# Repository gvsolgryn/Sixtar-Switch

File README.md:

# Sixtar-Switch
식스타 게이트 닌텐도 스위치 버전용 컨트롤러
# 지원기기
Nintendo Switch 및 Steam 을 지원하는 OS (Windows 10 및 11 에서 rp2040 펌웨어 테스트 완료)
# 디자인
키보드 형식을 기반으로 제작하였습니다 GAMO2 K28 을 보고 감명받아 제작을 시작하였습니다.
프로토타입으로만 제작해서 테스트 할 예정입니다.
(PCB는 만들 줄 알지만, 외관 및 기구 디자인은 잘 못하기도 하고, 아크릴 제작 단가가 높아서...)

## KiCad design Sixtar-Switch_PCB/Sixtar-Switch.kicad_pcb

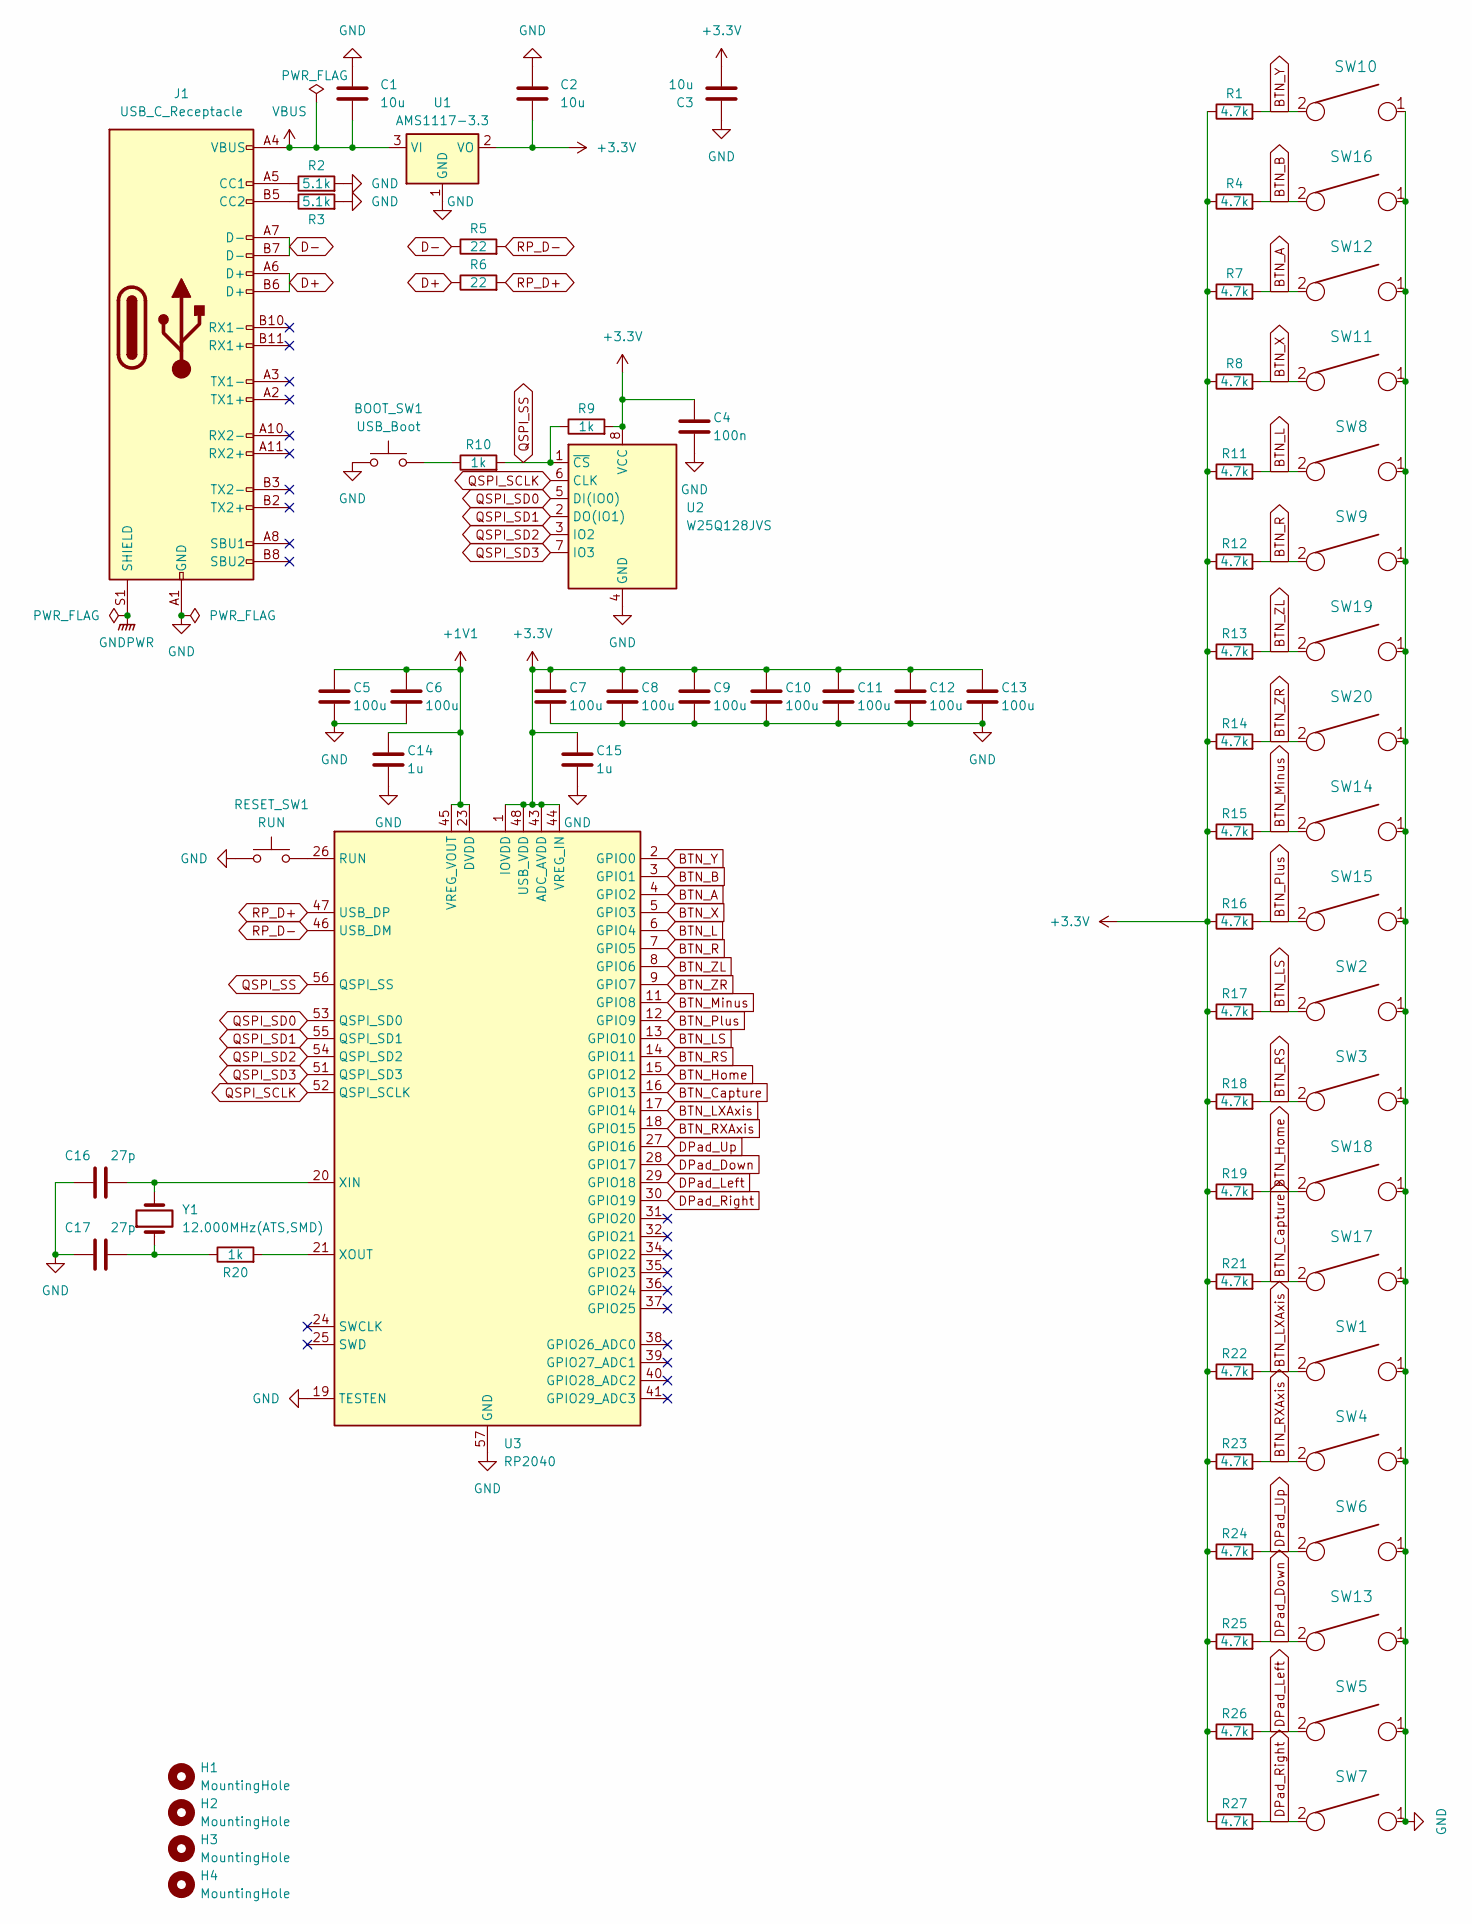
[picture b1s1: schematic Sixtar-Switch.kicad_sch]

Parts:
BOOT_SW1: USB_Boot; PinSocket_1x02_P2.54mm_Vertical
C1, C2, C3: 10u; C_0805_2012Metric_Pad1.18x1.45mm_HandSolder
C4: 100n; C_0805_2012Metric_Pad1.18x1.45mm_HandSolder
C5, C6, C7, C8, C9, C10, C11, C12, C13: 100u; C_0805_2012Metric_Pad1.18x1.45mm_HandSolder
C14, C15: 1u; C_0805_2012Metric_Pad1.18x1.45mm_HandSolder
C16, C17: 27p; C_0805_2012Metric_Pad1.18x1.45mm_HandSolder
H1, H2, H3, H4: MountingHole; MountingHole_3.2mm_M3
J1: USB_C_Receptacle; USB_C_Receptacle_XKB_U262-16XN-4BVC11
R1, R4, R7, R8, R11, R12, R13, R14, R15, R16, R17, R18, R19, R21, R22, R23, R24, R25, R26, R27: 4.7k; R_0805_2012Metric_Pad1.20x1.40mm_HandSolder
R2, R3: 5.1k; R_0805_2012Metric_Pad1.20x1.40mm_HandSolder
R5, R6: 22; R_0805_2012Metric_Pad1.20x1.40mm_HandSolder
R9, R10, R20: 1k; R_0805_2012Metric_Pad1.20x1.40mm_HandSolder
RESET_SW1: RUN; PinSocket_1x02_P2.54mm_Vertical
SW1, SW4, SW19, SW20: KEYSW; SW_Cherry_MX_2.00u_PCB
SW2, SW3, SW5, SW6, SW7, SW8, SW9, SW10, SW11, SW12, SW13, SW14, SW15, SW16, SW17, SW18: KEYSW; SW_Cherry_MX_1.00u_PCB
U1: AMS1117-3.3; SOT-223-3_TabPin2
U2: W25Q128JVS; SOIC-8_5.23x5.23mm_P1.27mm
U3: RP2040; QFN-56-1EP_7x7mm_P0.4mm_EP3.2x3.2mm
Y1: 12.000MHz(ATS,SMD); Crystal_SMD_5032-2Pin_5.0x3.2mm

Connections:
+1V1: C5.1, C6.1, C14.1, U3.23 (DVDD), U3.45 (VREG_VOUT), U3.50 (DVDD)
+3.3V: C2.2, C3.2, C4.1, C7.1, C8.1, C9.1, C10.1, C11.1, C12.1, C13.1, C15.1, R1.1, R4.1, R7.1, R8.1, R9.2, R11.1, R12.1, R13.1, R14.1, R15.1, R16.1, R17.1, R18.1, R19.1, R21.1, R22.1, R23.1, R24.1, R25.1, R26.1, R27.1, U1.2 (VO), U2.8 (VCC), U3.1 (IOVDD), U3.10 (IOVDD), U3.22 (IOVDD), U3.33 (IOVDD), U3.42 (IOVDD), U3.43 (ADC_AVDD), U3.44 (VREG_IN), U3.48 (USB_VDD), U3.49 (IOVDD)
BTN_A: R7.2, SW12.2, U3.4 (GPIO2)
BTN_B: R4.2, SW16.2, U3.3 (GPIO1)
BTN_Capture: R21.2, SW17.2, U3.16 (GPIO13)
BTN_Home: R19.2, SW18.2, U3.15 (GPIO12)
BTN_L: R11.2, SW8.2, U3.6 (GPIO4)
BTN_LS: R17.2, SW2.2, U3.13 (GPIO10)
BTN_LXAxis: R22.2, SW1.2, U3.17 (GPIO14)
BTN_Minus: R15.2, SW14.2, U3.11 (GPIO8)
BTN_Plus: R16.2, SW15.2, U3.12 (GPIO9)
BTN_R: R12.2, SW9.2, U3.7 (GPIO5)
BTN_RS: R18.2, SW3.2, U3.14 (GPIO11)
BTN_RXAxis: R23.2, SW4.2, U3.18 (GPIO15)
BTN_X: R8.2, SW11.2, U3.5 (GPIO3)
BTN_Y: R1.2, SW10.2, U3.2 (GPIO0)
BTN_ZL: R13.2, SW19.2, U3.8 (GPIO6)
BTN_ZR: R14.2, SW20.2, U3.9 (GPIO7)
D+: J1.A6 (D+), J1.B6 (D+), R6.1
D-: J1.A7 (D-), J1.B7 (D-), R5.1
DPad_Down: R25.2, SW13.2, U3.28 (GPIO17)
DPad_Left: R26.2, SW5.2, U3.29 (GPIO18)
DPad_Right: R27.2, SW7.2, U3.30 (GPIO19)
DPad_Up: R24.2, SW6.2, U3.27 (GPIO16)
GND: BOOT_SW1.1, C1.1, C2.1, C3.1, C4.2, C5.2, C6.2, C7.2, C8.2, C9.2, C10.2, C11.2, C12.2, C13.2, C14.2, C15.2, C16.1, C17.1, J1.A1 (GND), J1.A12 (GND), J1.B1 (GND), J1.B12 (GND), R2.2, R3.2, RESET_SW1.1, SW1.1, SW2.1, SW3.1, SW4.1, SW5.1, SW6.1, SW7.1, SW8.1, SW9.1, SW10.1, SW11.1, SW12.1, SW13.1, SW14.1, SW15.1, SW16.1, SW17.1, SW18.1, SW19.1, SW20.1, U1.1 (GND), U2.4 (GND), U3.19 (TESTEN), U3.57 (GND)
GNDPWR: J1.S1 (SHIELD)
unnamed: BOOT_SW1.2, R10.1
unnamed: C17.2, R20.1, Y1.1
unnamed: J1.A5 (CC1), R2.1
unnamed: J1.B5 (CC2), R3.1
unnamed: RESET_SW1.2, U3.26 (RUN)
unnamed: C16.2, U3.20 (XIN), Y1.2
unnamed: R20.2, U3.21 (XOUT)
QSPI_SCLK: U2.6 (CLK), U3.52 (QSPI_SCLK)
QSPI_SD0: U2.5 (DI(IO0)), U3.53 (QSPI_SD0)
QSPI_SD1: U2.2 (DO(IO1)), U3.55 (QSPI_SD1)
QSPI_SD2: U2.3 (IO2), U3.54 (QSPI_SD2)
QSPI_SD3: U2.7 (IO3), U3.51 (QSPI_SD3)
QSPI_SS: R9.1, R10.2, U2.1 (~CS), U3.56 (QSPI_SS)
RP_D+: R6.2, U3.47 (USB_DP)
RP_D-: R5.2, U3.46 (USB_DM)
VBUS: C1.2, J1.A4 (VBUS), J1.A9 (VBUS), J1.B4 (VBUS), J1.B9 (VBUS), U1.3 (VI)

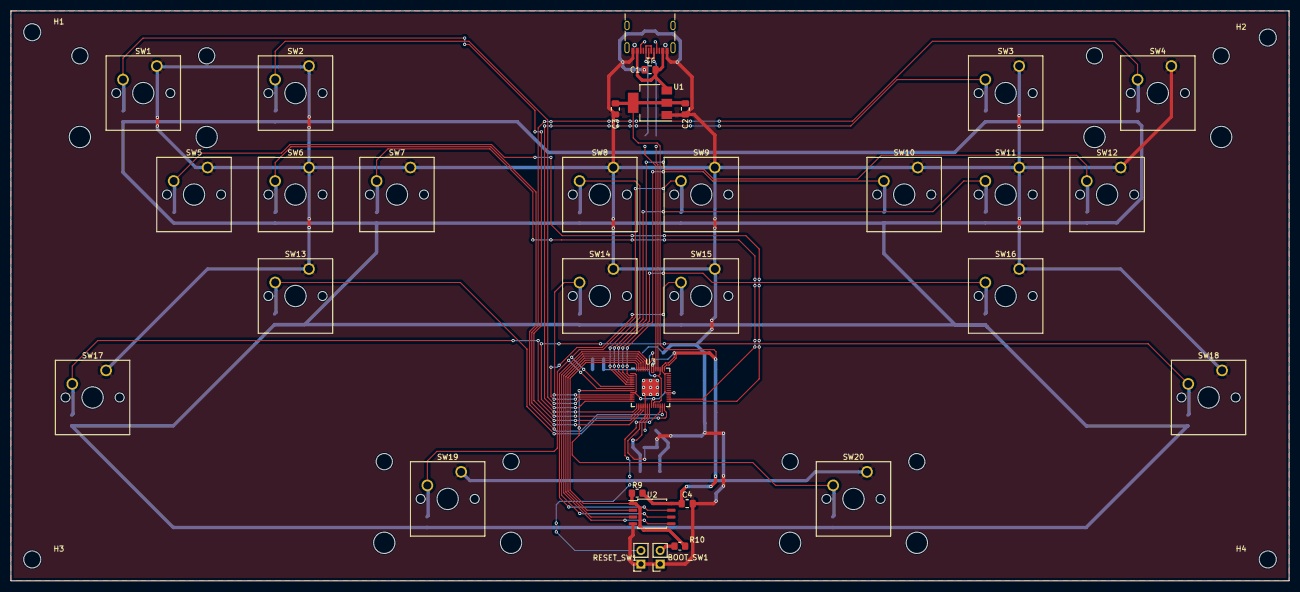
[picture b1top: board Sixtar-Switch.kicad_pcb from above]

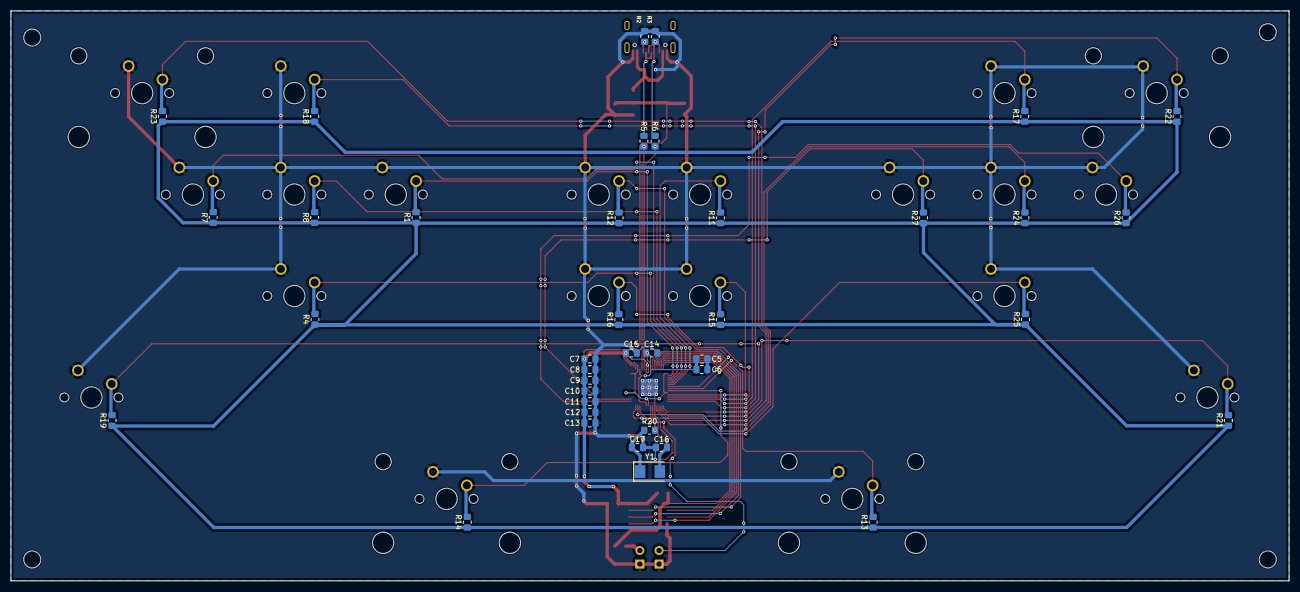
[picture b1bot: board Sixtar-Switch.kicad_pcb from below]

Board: 2 copper layers, 240.0 x 107.0 mm, 75 parts (39 on the bottom side), 41 nets.

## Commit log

2023-04-03 add gitignore
2023-04-03 KiCad Project init
2023-04-03 Add Keyboard Library
2023-04-03 Add new Directory for PCB
2023-04-03 Init Arduino Workspace
2023-05-09 RPi-Pico SDK Submodule 설정
2023-05-09 RP2040 Firmware Init
2023-05-10 gitsubmodule 제거
2023-05-10 펌웨어 코드 위치 변경
2023-05-10 includepath 변경(진행중)
2023-05-10 SwitchControlLibrary 추가(포팅필요)
2023-05-10 add CMake Build System
2023-05-10 폴더 이름 변경 및 폴더 위치 변경
2023-05-10 tiniusb 지원을 위해 코드 추가
2023-05-10 .gitignore 추가
2023-05-10 vscode setting 수정
2023-05-10 tinyusb 빌드를 위해 수정
2023-05-10 pico-example 코드로 변경
2023-05-10 GamePad 기초 테스트 코드로 수정
2023-05-10 VID PID 수정 및 GamePad 로만 인식하도록 수정
2023-05-11 .vscode 폴더 업로드 안하도록 .gitignore 수정
2023-05-11 gitignore 수정 및 git 캐시삭제
2023-05-12 GamePad HID 전송 안되던 오류 수정
2023-05-12 코드 수정중
2023-05-15 코드 위치 변경 (src -> src/include)
2023-05-15 코드 위치 변경에 따른 CMakeLists 변경
2023-05-15 포팅 or 참조용 코드 위치 변경
2023-05-15 불필요한 코드 삭제
2023-05-15 switchControllLibrary 참조하여 헤더 추가
2023-05-15 테스트용 코드 수정 - boot 버튼 누를 시 Hat UP 하도록 수정
2023-05-16 rp2040 HID Gamepad 기초 코드 작성
2023-05-16 들여쓰기 4 -> 공백 4 로 변경
2023-05-16 nintendo switch joystick report (테스트 필요)
2023-05-16 버그 수정중 - HID 인식 안됨 - 포팅을 다시 진행해야함
2023-05-18 닌텐도 스위치용 HID 디스크립터 변경
2023-05-18 스위치 작동 확인 하지만 버그 발견 - 엔디안 오류가 있는 것 같음
2023-09-18 gitignore 수정
2023-09-18 소스코드 테스트중...
2023-09-18 test
2023-09-19 디렉터리 정리
2023-09-19 Raspberry Pi Pico C/C++ SDK 이용 스위치 컨트롤러 코드 수정 완료 - GPIO0 ~ GPIO13에 버튼값들 할당 완료 - HAT 및 다른 기능들 추가 해야함
2023-09-19 닌텐도 스위치의 모든 버튼 및 axis 작동 확인 - GPIO0 ~ 13 = 스위치 버튼 Y, B, A, X, L트리거, R트리거, ZL트리거, ZR트리거, 마이너스, 플러스, L스틱, R스틱, 홈, 캡쳐 - GPIO14 = L스틱 왼쪽방향으로 틀기 - GPIO15 = R스틱 오른쪽방향으로 틀기
2023-09-19 닌텐도 스위치의 dPad 버튼 작동 확인 - GPIO15 ~ 18 = up, down, left, right 로 매핑
2023-09-19 pin 중복 할당 수정
2023-09-19 kicad 회로 수정
2023-09-25 KiCAD 회로 수정 및 PCB 제작중
2023-09-25 키 배치 수정
2023-09-25 저항 배치중
2023-09-26 저항 배치 및 배선 그리는중
2023-10-04 PCB빌드 완료. 테스트 필요
2023-10-04 3d 모델 완성
2023-10-04 이미지 추가
2023-10-05 PCB via hole 잘못되서 처음부터 다시 라인 작업해야함
2023-10-05 배선 수정 및 via hole 수정
